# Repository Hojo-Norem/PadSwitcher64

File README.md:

# PadSwitcher64

Interface to allow Super Nintendo (SNES) control pads to be plugged into a C64's joystick ports.

The adapter connects to both C64 joystick ports and allows the active port to be changed on the fly with a push of a button.  The interface defaults to joystick port two on power on.

Also, the interface allows up to four custom mappings to be programmed using a C64-side application.  The custom mappings allow any combination of joystick port two and port one control lines to be mapped to any of the Super Nintendo controller action buttons (A,B,X,Y,L,R).  Any of the action buttons can also have an optional rapid-fire function applied, of which a normal and 'inverted' state is available.  'Inverted' rapid fire is simply that when active the output state of the effected button will be opposite to of a normal rapid fire button when pushed.  For example, mapping a button to joystick left with rapid fire and another button to joystick right with inverted rapid fire will simulate a rapid left/right joystick waggle when both buttons are pushed.

This code was originally developed for the Atmel ATMega8 mcu and was then later ported over to the ATMega88.  This was mainly due to the availability of the Mega8 and that the Mega88 has more power saving features.

This source code was written using AVR-GCC and AVR Libc.  The C64-side software was written in Notepad++, tokenised to CBM BASIC using C64List and then compiled using "BASIC 64".  The machine code portion was assembled using 64tass.

**A pre-compiled HEX file for the AVR and the C64-side software for setting the custom mappings can be found in the releases section.  Once sucessfully programmed, the LED indicator will flash for a couple of seconds on every subsiquent power-on.**

**Mega88 fuse settings: CKDIV8 disabled, all other fuses at factory defaults.**

**PCB has been uploaded to OSH Park ( https://oshpark.com/shared_projects/Fk2LAkUS ) where they can be ordered in multiples of three.**
	
# TODO :
  * Re-jig command mode for potential compatibility with non-C64 Atari joystick compatible machines.
  * Maybe figure out how to support two pads while still retaining some semblance of mapping support.
	
# Pad Mapping: (default)
|SNES|C64|
|---|---|
|DPAD UP|UP|
|DPAD DOWN|DOWN|
|DPAD LEFT|LEFT|
|DPAD RIGHT|RIGHT|
|Y|FIRE|
|X|TURBO FIRE|
|B|UP|
|A|'Special'(*1)|
|R|KEYBOARD MATRIX LINE(PORT 2 MODE ONLY)(*2)|

(*1) -  UP + FIRE or DOWN + FIRE, swapped with SELECT + L.

(*2) - Defaults to PB4 which most software will interpret as the SPACEBAR.

# Fixed Controls:
|Button/Combo|Function|
|---|---|
|SELECT + UP|Toggle disable of D-PAD UP|
|START|Swap Joystick control port|
|SELECT + L|Toggle 'Special' function|
|SELECT + R|Change keyboard matrix line (*3)|
|SELECT + DOWN|Toggle TURBO FIRE rate|
|SELECT + (A,B,X,Y)|Select mapping| 
|SELECT + START|Default Mapping|	
|SELECT + START|Enter Command Mode (*4)| 
|SELECT + START + L + R| |
|(In normal or mapped mode)|Enter type 1 direct mode|
|(In any other mode)|Force normal mode|

(*3) - Joystick port 1, which corresponds to CIA 1 PB0 to PB4, PB4 which are normally used as the keyboard input lines during keyboard scanning.  By default at startup this is set to PB4, which most software will interpret as the SPACEBAR.
|CIA1 PortB|CIA1 PA7|PA6|PA5|PA4|PA3|PA2|PA1|PA0|
|---|---|---|---|---|---|---|---|---|
|**PB4**|SPACE|R-SHIFT|.|M|B|C|Z|F1/F2|
|**PB3**|2|CLR/HOME|-|0|8|6|4|F7/F8|
|**PB2**|CTRL|;|L|J|G|D|A|CRSR|->/<-|
|**PB1**|<-|*|P|I|Y|R|W|RETURN|
|**PB0**|1|£|+|9|7|5|3|INST/DEL|

(*4) - Only functional when prompted, only functional in default mapping mode.

# MAPPING
Four mappings, each with all 6 action buttons available.  Each button has a 2 byte pattern corresponding to the following:
|Byte/Bit|Function|
|---|---|
|Byte 1 - Bit 0 to 3|PB0 to PB3 (JOY 1 Directions & KB matrix)|
|Byte 1 - Bit 4 to 7|PA0 to PA3 (Joy 2 directions)|
|Byte 2 - Bit 0|PB4 (Joy 1 Fire & KB matrix)|
|Byte 2 - bit 1|PA4 (Joy 2 Fire)|
|Byte 2 - bit 2|Pad Button has turbofire action|
|Byte 2 - Bit 3|Pad Button has turbofire action (inverted)|
		
Bits 4 - 7 of byte 2 are not accessible through the command interface at this time.
			
# Direct mode - Type 1
Direct mode allows all the SNES control pad buttons to be read by the C64.  Type 1 uses both joystick port to report all buttons.  There is technically a direct mode type 2, and that is by using the command interface.  Type one is much faster as it just involves reading the joystick ports normally. 
|SNES Pad|C64 CIA|Bit pattern|C64 Joystick|
|---|---|---|---|
|Up|DC00| 11110|Port 2 up|
|Down|DC00|11101|Port 2 down|
|Left|DC00|11011|Port 2 left|
|Right|DC00|10111|Port 2 right|
|Y|DC00|01111|Port 2 fire|
|Start|DC00|00000|Port 2 all|
|B|DC01|11110|Port 1 up|
|X|DC01|11101|Port 1 down|
|L|DC01|11011|Port 1 left|
|R|DC01|10111|Port 1 right|
|A|DC01|01111|Port 1 fire|
|Select|DC01|00000|Port 1 all|

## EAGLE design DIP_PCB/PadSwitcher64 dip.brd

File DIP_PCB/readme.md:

# BOM

1 x Atmel/Microchip AVR ATMega88 in 28 pin DIP package.  Any speed grade will do.

(Optional) 1 x 28 pin DIP socket.  If you ommit this part the the resistor will need to be soldered
  to the reverse side of the PCB, taking care to leave as little amount of leg protruding underneath
  as possible.

1 x 330 Ohm resistor

1 x LED (any regualr LED will do)

1 x 100nF ceramic capacitor

1 x 100uF electrolytic capacitor

1 x 3-by-2 pin header.  Optional if you are going to program the AVR out of circuit.

1 x SNES control port socket.  Straight pin or right angled by your preference.  The PCB is able to accomodate
  the sockets that use the thicker pins.

2 x Female DB9 plug/socket with straight PCB mounts.  When soldering I recommend spacing them out from the PCB
  a couple of mm.

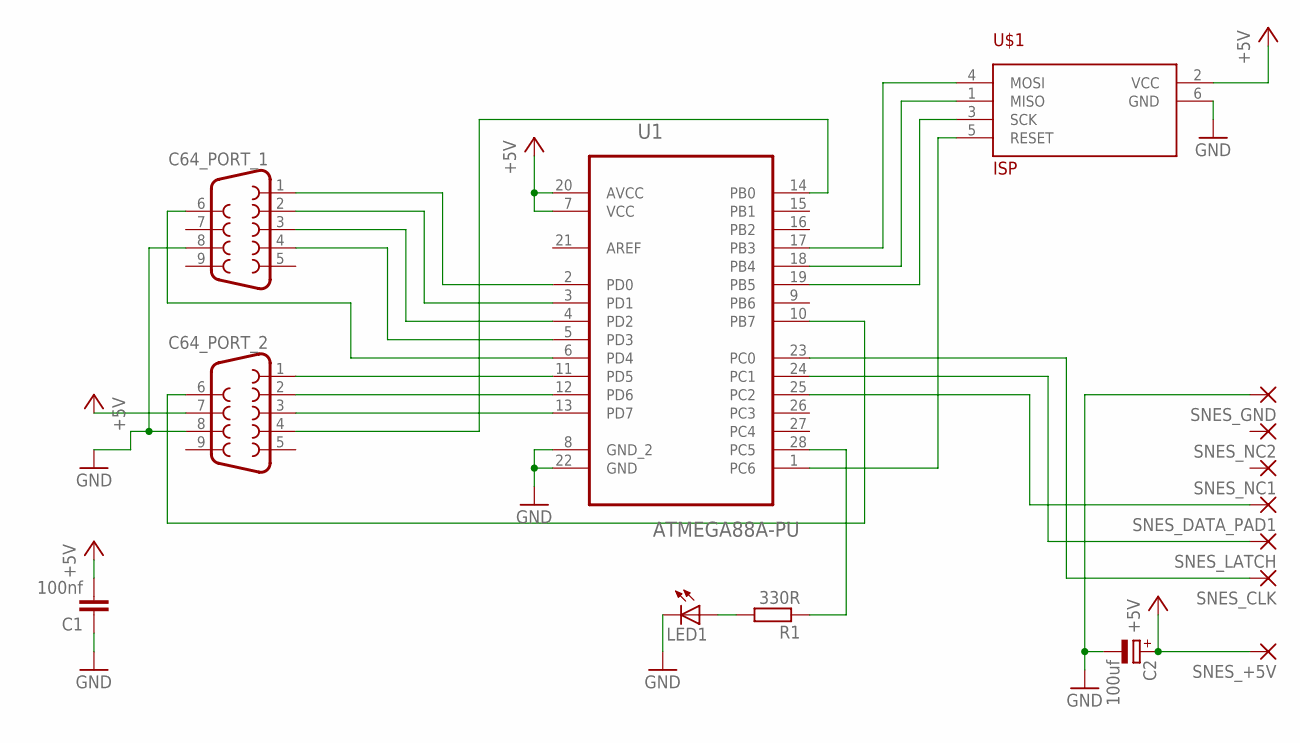
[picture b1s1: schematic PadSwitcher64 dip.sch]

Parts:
C1: 100nf; C050-024X044
C2: 100uf; E2,5-5
C64_PORT_1, C64_PORT_2: F09; F09VB_NO_SHELL
LED1: LEDSQR2X5; LED2X5
R1: 330R; 0207/10
SNES_+5V: 3,17/1,1
SNES_CLK: 3,17/1,1
SNES_DATA_PAD1: 3,17/1,1
SNES_GND: 3,17/1,1
SNES_LATCH: 3,17/1,1
SNES_NC1, SNES_NC2: 3,17/1,1
U1: ATMEGA88A-PU; DIL28-3
U$1: ISP; MA03-2

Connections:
+5V: C1.2, C2.+, C64_PORT_2.7, SNES_+5V.1, U1.7 (VCC), U1.20 (AVCC), U$1.2 (VCC)
GND: C1.1, C2.-, C64_PORT_1.8, C64_PORT_2.8, LED1.K (C), SNES_GND.1, U1.8 (GND_2), U1.22 (GND), U$1.6 (GND)
unnamed: U1.1 (PC6), U$1.5 (RESET)
unnamed: U1.19 (PB5), U$1.3 (SCK)
unnamed: U1.18 (PB4), U$1.1 (MISO)
unnamed: U1.17 (PB3), U$1.4 (MOSI)
unnamed: C64_PORT_1.1, U1.2 (PD0)
unnamed: C64_PORT_1.2, U1.3 (PD1)
unnamed: C64_PORT_1.3, U1.4 (PD2)
unnamed: C64_PORT_1.4, U1.5 (PD3)
unnamed: C64_PORT_1.6, U1.6 (PD4)
unnamed: C64_PORT_2.6, U1.10 (PB7)
unnamed: C64_PORT_2.1, U1.11 (PD5)
unnamed: C64_PORT_2.2, U1.12 (PD6)
unnamed: C64_PORT_2.3, U1.13 (PD7)
unnamed: C64_PORT_2.4, U1.14 (PB0)
unnamed: SNES_CLK.1, U1.23 (PC0)
unnamed: SNES_LATCH.1, U1.24 (PC1)
unnamed: SNES_DATA_PAD1.1, U1.25 (PC2)
unnamed: R1.1, U1.28 (PC5)
unnamed: LED1.A, R1.2

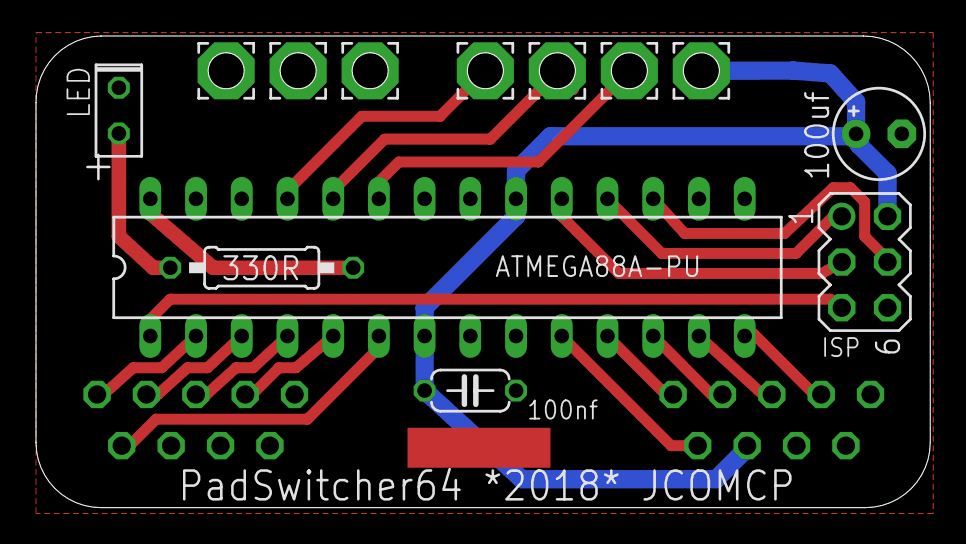
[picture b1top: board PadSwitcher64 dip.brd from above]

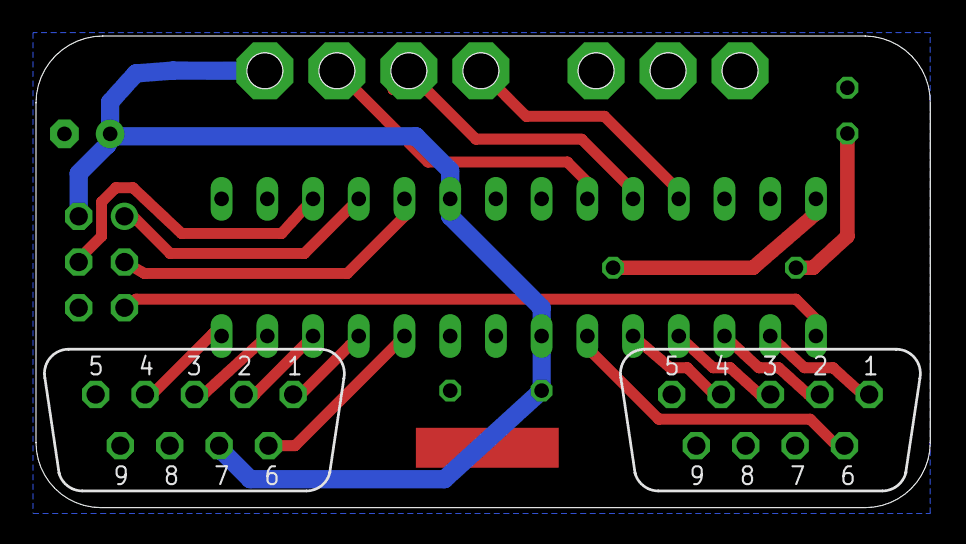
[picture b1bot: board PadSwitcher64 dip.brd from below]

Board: 2 copper layers, 49.7 x 26.2 mm, 15 parts (2 on the bottom side), 21 nets.

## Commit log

2020-05-06 Create brargh
2020-05-06 CPU divisor and TURBO FIRE
    I wasn't setting the CPU clock divisor properly. Was running at 8Mhz instead of 4. Now Fixed. Lower speed = less power needed. Also means that the pad reading routine is running at correct speed.
    Also, added ability to switch between two TURBO FIRE speeds. Use SELECT + DOWN to toggle between FAST and NOT-SO-FAST. Some games don't respond properly to fast turbo fire rates.
    Why do I always find these things AFTER I publish?
2020-05-06 Added turbo fire speed toggle
2020-05-07 Fixed command interface broken with last commit
2020-05-09 Fixed being unable to enter direct mode
2020-07-29 Attempt at NTSC timeout fix
    All I did was triple the maximum timeout. PAL still works fine but I don't have a NTSC machine to test with.
2020-09-09 Another attempt at a NTSC fix
    Please read https://github.com/Hojo-Norem/PadSwitcher64/issues/1 for further information.
2020-09-27 Added extra info on AVR, SNES socket and DB9s
2020-09-27 Added extra info on AVR, DIP socket, SNES socket and DB9s
2020-09-27 Fixed component values on silkscreen.
2020-09-27 Upload C64 side software sourcecode and add GPL headers
2020-09-27 Adjusted component positions.
    Turns out that there wasn't enough room to mount the straight pin SNES socket properly. The PCB has been enlarged a smidgen and the AVR and socket have been moved apart a little.
2020-09-27 Adjusted component positions... again.
    Forgot to nudge the LED out to the way a little.
2020-09-27 Add AVR fuse settings and PCB link
2021-05-05 Fixed timer inicialization - or at least made it more portable

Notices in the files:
DIP_PCB/PadSwitcher64 dip.brd:
modify it under the terms of the GNU General Public License as published
DIP_PCB/PadSwitcher64 dip.sch:
PadSwitcher64 is free software / hardware: you can redistribute it and/or modify
it under the terms of the GNU General Public License as published by
the Free Software Foundation, either version 3 of the License, or
(at your option) any later version.
